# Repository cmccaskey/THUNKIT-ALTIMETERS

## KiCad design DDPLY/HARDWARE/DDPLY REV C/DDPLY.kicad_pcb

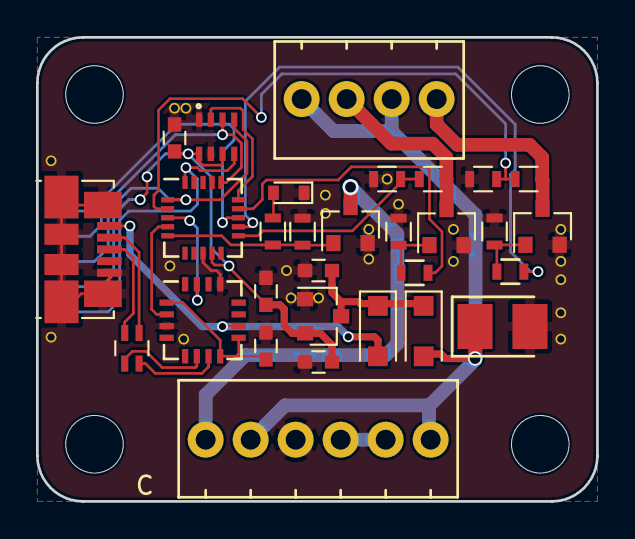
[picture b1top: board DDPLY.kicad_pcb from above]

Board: 2 copper layers, 31.1 x 25.8 mm, 31 parts (1 on the bottom side), 29 nets.

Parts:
C1, C2, C3, C4, C8: 1uF; C_0603
C6: 100uF; Tantalum_Case-B_EIA-3528-21_Reflow
D1, D2: D_Schottky; D_SOD-123F
D3: RED; D_0603
P1: USB_OTG; USB_Micro-B_Molex_47346-0001
P2: SCREW; 100MIL_STX4
P3: SCREW; 100MIL_STX6
P5: ICSP; LINEAR_ICSP
Q1, Q2, Q3: Q_NJFET_GSD; SOT-23
R1: 22; R_Array_Concave_2x0603
R2, R3, R4: 680; R_0603
R7, R8, R9, R11, R13: 10K; R_0603
R10, R12: 100K; R_0603
U1: AP2210; SOT-23
U2: FT230XQ-R; QFN-16_4x4mm_Pitch0.65mm
U4: BMP280; LGA-8_PIN1_DOT
U5: ATTINY841-MMH; QFN-20-1EP_4x4mm_Pitch0.5mm

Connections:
+3V3: C1.1, C4.1, C8.1, P5.2, U1.2, U4.6, U4.8, U5.9
+5V: D2.2, P1.1, U2.10
+9V: C6.1, D1.2, P2.2, P2.4, P3.2, P3.6
CONT_1: R10.2, R11.1, U5.11
CONT_2: R12.2, R13.1, U5.2
CS_BMP: U4.2, U5.15
E-M1: P2.3, Q1.3, R10.1
E-M2: P2.1, Q2.3, R12.1
E-MATCH_1: R3.2, U5.14
E-MATCH_2: R4.2, U5.12
GND: C1.2, C2.2, C3.2, C4.2, C6.2, C8.2, D3.1, P1.5, P1.6, P3.3, P5.6, Q1.2, Q2.2, Q3.2, R7.2, R8.2, R9.2, R11.2, R13.2, U1.1, U2.3, U2.13, U4.1, U4.7, U5.8
MISO_AVR: P5.1, U4.5, U5.20
MOSI_AVR: P5.4, U4.3, U5.16
unnamed: C2.1, U2.1, U2.8, U2.9
unnamed: C3.1, D1.1, D2.1, U1.3
unnamed: D3.2, R2.2
unnamed: P1.2, R1.1
unnamed: P1.3, R1.2
unnamed: P3.4, P3.5
unnamed: Q1.1, R3.1, R7.1
unnamed: Q2.1, R4.1, R8.1
unnamed: R1.3, U2.6
unnamed: R1.4, U2.7
PIEZO: Q3.1, R2.1, R9.1, U5.5
PIEZO_OUT: P3.1, Q3.3
RST_AVR: P5.5, U5.13
RX_AVR: U2.15, U5.3
SCK_AVR: P5.3, U4.4, U5.1
TX_AVR: U2.2, U5.4

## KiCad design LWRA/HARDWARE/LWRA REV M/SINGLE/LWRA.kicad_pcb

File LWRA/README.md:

# About #

The Light Weight Rocket Altimeter (LWRA) is a an attempt at the simplest and lightest
rocket altimeter on the market. A lightweight altimeter can see use in altitude competitions
such as the Team America Rocketry Challenge (TARC) and FAI competitions where weight and space
for an altimeter in a rocket is at a premium. Recent versions include built in data logging without
an external dongle or tool.

| Front | Back |
| ---------------------------------------------- | --------------------------------------------- |
|   |   |

# Hardware History #

## Current Version ##
## REV I ##
- Current version
- Uses the ATTiny841 with the FT230X to interface with the computer
- Same form factor and battery as REV H
- Battery connector offers a point to tether the altimiter inside the rocket
- Uses the CR1216, CR1220, or CR1225 batteries which are easy to replace
- Size was less of a concern on this version allowing user interface and cost to be the main concern

## Previous Versions ##
## REV A ##
- First design used ATTiny85 and MPL3115A2 pressure sensor
- The wrong pins were used to interface with the sensor
- Used a CR1216 coin cell battery
## REV B ##
- Used the ATTiny841 with the BMP280 pressure sensor for its reduced cost
- Included an FT230X USB to serial adapter to interface with the computer
- Had a small 5.8mAh 3V battery on the back of the PCB
- Battery life was limited and lacked a proper battery charging circuit. 
- The ATTiny841 only supports I2C slave and not master functionallity that was needed to interace with the BMP280
## REV C ##
- Used the ATmegaXXU2 series microcontrollers.
- HWB pin on the MCU was not connected to GND so it wasn't possible to program the MCU
- Used a 1.5V button cell with boost regulator, however the battery couldn't provide enough current
## REV D ##
- Fixed the HWB pin issue
## REV E ##
- Moved back to the ATTiny841 because of issues with LUFA
- Used same battery and regulator circuit as REV D
- UART adapter was external from the board therefore requiring a dongle
- Misc. pinout issues
## REV F ##
- Same as REV E with updated pinout on ICSP connector
## REV G ##
- Updated version of REV D with mounting hole
## REV H ##
- Moved to same form factor as REV A for easier use and reduced BOM cost
- Still used ATmegaXXU2 series MCUs
- CR1216 and CR1220 couldn't supply a high enough voltage under load to prevent the MCU from brown out

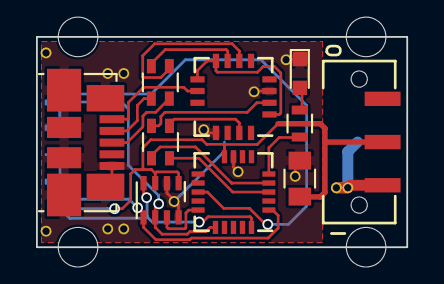
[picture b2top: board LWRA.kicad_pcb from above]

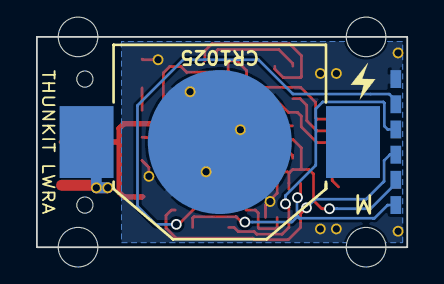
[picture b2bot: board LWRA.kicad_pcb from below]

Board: 2 copper layers, 20.6 x 11.7 mm, 12 parts (2 on the bottom side), 20 nets.

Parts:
BT1: 3V; BK-870
C1: 1uF; C_0805
D1: LED; LED_0603
P1: USB_OTG; USB_Micro-B_Molex_47346-0001
P2: ICSP; LINEAR_ICSP
R1: 22; R_Array_Convex_2x0603
R2: 1K; R_Array_Convex_2x0603
R3: 330; R_0603
SW1: Push_SW; JS102011JAQN_Handsoldering
U1: BMP280; LGA-8_NO_DOT
U2: ATTINY841-MU; QFN-20-1EP_4x4mm_Pitch0.5mm_NO_PIN_10
U3: FT230XQ-R; QFN-16_4x4mm_Pitch0.65mm_NO_PIN_12

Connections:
/PWR: BT1.1, SW1.1
BMP_CS: U1.2, U2.15
GND: BT1.2, C1.2, D1.1, P1.5, P1.6, P2.6, U1.1, U1.7, U2.8, U3.3, U3.13
MISO: P2.1, U1.5, U2.20
MOSI: P2.4, U1.3, U2.16
unnamed: D1.2, R3.1
unnamed: P1.1, U3.10
unnamed: P1.2, R1.1
unnamed: P1.3, R1.2
unnamed: R1.3, U3.6
unnamed: R1.4, U3.7
unnamed: R2.1, U3.15
unnamed: R2.2, U3.2
unnamed: R3.2, U2.5
unnamed: U3.1, U3.8, U3.9
RST: P2.5, U2.13
RX_FTDI: R2.3, U2.4
SCK: P2.3, U1.4, U2.1
TX_FTDI: R2.4, U2.3
VCC: C1.1, P2.2, SW1.2, U1.6, U1.8, U2.9

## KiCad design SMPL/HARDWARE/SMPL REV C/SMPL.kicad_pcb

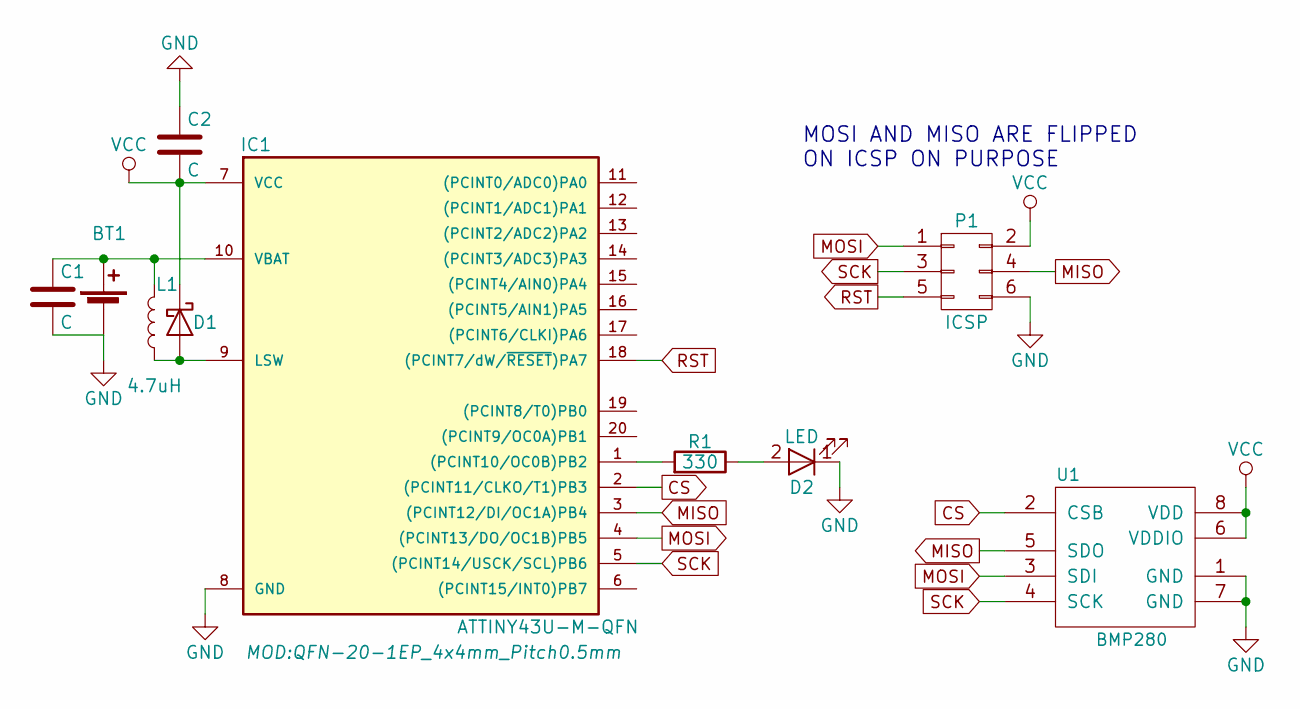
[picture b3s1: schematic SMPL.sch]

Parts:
BT1: Battery_Cell; 1376164-1
C1, C2: C; C_0402
D1: D_Schottky; C_0603
D2: LED; LED_0603
IC1: ATTINY43U-M-QFN; QFN-20-1EP_4x4mm_Pitch0.5mm
L1: 4.7uH; C_0603
P1: ICSP; 2.54 ICSP
R1: 330; R_0402
U1: BMP280; LGA-8_NO_DOT

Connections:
CS: IC1.2 ((PCINT11/CLKO/T1)PB3), U1.2 (CSB)
GND: BT1.2 (-), C1.2, C2.1, D2.1 (K), IC1.8 (GND), P1.6, U1.1 (GND), U1.7 (GND)
MISO: IC1.3 ((PCINT12/DI/OC1A)PB4), P1.4, U1.5 (SDO)
MOSI: IC1.4 ((PCINT13/DO/OC1B)PB5), P1.1, U1.3 (SDI)
unnamed: BT1.1 (+), C1.1, IC1.10 (VBAT), L1.2
unnamed: D1.2 (A), IC1.9 (LSW), L1.1
unnamed: D2.2 (A), R1.1
unnamed: IC1.1 ((PCINT10/OC0B)PB2), R1.2
RST: IC1.18 ((PCINT7/dW/~RESET~)PA7), P1.5
SCK: IC1.5 ((PCINT14/USCK/SCL)PB6), P1.3, U1.4 (SCK)
VCC: C2.2, D1.1 (K), IC1.7 (VCC), P1.2, U1.6 (VDDIO), U1.8 (VDD)

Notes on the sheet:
MOSI AND MISO ARE FLIPPED ON ICSP ON PURPOSE

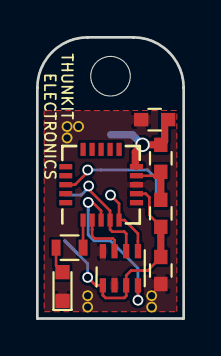
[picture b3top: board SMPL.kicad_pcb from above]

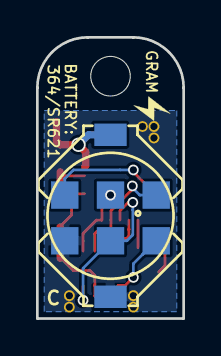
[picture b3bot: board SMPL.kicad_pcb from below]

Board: 2 copper layers, 8.1 x 15.6 mm, 10 parts (2 on the bottom side), 11 nets.

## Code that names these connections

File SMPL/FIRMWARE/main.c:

// avrdude -U lfuse:w:0xE2:m -c usbtiny -p attiny43u

#define F_CPU 8000000UL

#define LED_ON PORTB |= (1 << PB2)
#define LED_OFF PORTB &= ~(1 << PB2)

#define launchTrigger 2 // feet in pollingDelay
#define bootDelay 5000   // delay in mS
#define pollingDelay 100 // mS

#define altitudeOffset 1000

#define expWeight 0.5 // closer to 0 favors old var, closer to 1 favors new var

#include <avr/eeprom.h>
#include <avr/io.h>
#include <stdbool.h>
#include <util/delay.h>
#include "Libraries/BMP280.h" //this must go after all other #includes

void blinkAltitude(void) {
  int maxAltitude = 0;
  int i;
  for (i = 0; i < 62; i += 2) {
    int currentAltitude = eeprom_read_word((uint16_t *)i);
    if (eeprom_read_word((uint16_t *)i) > maxAltitude) {
      maxAltitude = currentAltitude;
    }
  }
  if (maxAltitude == 0){
    return;
  }
  char altitudeBlinks;
  for (i = 4; i >= 0; i--) {
    if (maxAltitude % 10 == 0) {
      altitudeBlinks = 10;
    } else {
      altitudeBlinks = maxAltitude % 10;
    }
    maxAltitude /= 10;
    int j;
    for (j = 0; j < altitudeBlinks; j++) {
      LED_ON;
      _delay_ms(200);
      LED_OFF;
      _delay_ms(200);
    }
    _delay_ms(1500);
  }
}

int main() {
  bool LED = false;
  bool launch = false;
  DDRB |= (1 << PB2) | (1 << PB5) | (1 << PB6) |
          (1 << PB3); // LED SCK MOSI CS output 5 6 3
  USICR |= (1 << USIWM0) | (1 << USICS1) | (1 << USICS0) | (1 << USITC); //| (1 << USICS1)
  LED_ON;
  /*    CHECK BMP280 ID    */
    PORTB |= (1 << PB3);

  _delay_ms(500);
  char ID;
  ID = SPI_RW_8(0xD0, 0x00);

  while (ID != 0x58) {
    LED_ON;
  }
  LED_OFF;
  LED = false;

  _delay_ms(100);
  BMP_Normal_Mode();
  _delay_ms(100);
  BMP_Set_Calib_Vars();
  //blinkAltitude();
  _delay_ms(bootDelay); //give time for things to settle
  // sei();
  BMP_Pressure_Cal = BMP_Pressure();
  uint32_t altitudeOld = BMP_Altitude(); // init this variable
  int eepromIndex = 0;
  while (1) {
    /*    EXPONENTIAL FILTER    */
    uint32_t altitudeNew =
        expWeight * BMP_Altitude() + (1.0 - expWeight) * altitudeOld;

    /*    DETECT LAUNCH    */
    if (!launch) {
      if (altitudeNew > altitudeOld + launchTrigger) {
        launch = true;
        int i;
        for (i = 0; i < 62; i += 2) {
          eeprom_write_word((uint16_t *)i, (uint16_t)1000);
        }
        eeprom_write_word((uint16_t *)0, (uint16_t)altitudeOld);
      }
    }

    altitudeOld = altitudeNew;

    if (launch) {
      if (eepromIndex < 62) {
        eeprom_write_word((uint16_t *)eepromIndex, (uint16_t)altitudeNew);
        eepromIndex += 2;
      }
    }

    if (!launch && !LED) {
      LED_ON;
      LED = true;
    } else if (LED){
      LED_OFF;
      LED = false;
    }
    if (launch){
      LED_OFF;
    }
    _delay_ms(pollingDelay);
  }
}

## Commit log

2018-07-07 init
2018-09-09 file recovery and updates
2018-09-11 fixed pin 1 dot on LWRA, firmware folder renamed
2018-09-12 LWRA BOM fix
2018-09-24 added gate resistors DDPLY
2018-09-25 fuses script for LWRA
2018-09-25 Fuses script for DDPLY
2018-10-04 BOD fix
2018-10-04 updated gui
2018-10-07 huge updates
2018-10-10 linux binary
2018-10-10 removed extra gitignore s
2018-10-10 added fast ulp upload to makefile
2018-10-10 now using 512KHz clock
2018-10-10 make clean
